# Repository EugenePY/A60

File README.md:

# Forest 65 PCB

Hi, Andrew nice work!

Since you are using the web based eda tool, I generaly do not have any problems 
with them. It's very simple and having great integration with the pcb/eletronic 
component firms, but I suggest you still need to learn KiCAD, 

There are few benifit about kicad. 

1. it's open sourced.
2. it has a great supported by the eda/keyboard community.

Most of open sourced EE project are using kicad as their tools, and some of 
professional still prefer it to some commercial EDAs like EAGLE, Altium. 

there are many learning resource for kicad, one of most popular one is the 
[Ai03's Keyboard Guide](https://wiki.ai03.com/books/pcb-design/page/pcb-guide-part-1---preparations)

You may follow it to know how to use kicad. Kicad also has a lot of open sourced footprint libarary.

1. [Ai03's Mx Switch Footprint](https://github.com/ai03-2725/MX_Alps_Hybrid.git)
2. [Acherion Project Gondolindrim](https://github.com/AcheronProject)

# For current PCB files

I  add datasheet about ATMEGA32U4-AU, you can check your pins, reading the 
datasheet maybe very overwhelming in the first place, but I still recommanded 
to go through it. It's very benifitcial for you in the long run since you want 
to get into eletronic desin/EE. And other datasheet follows the similar priciple.

# TODOs

1. Please rewire your pcb in kicad.

# PCB comments

I think your pcb works, but there are few things need to be improved.
    
### The wire should not be too close to the pcb edge if the space allowed. 

    If the wire are too close to the edge it may break easily, but it just a 
    minor things to notice, generaly it does not affect overall functionality.

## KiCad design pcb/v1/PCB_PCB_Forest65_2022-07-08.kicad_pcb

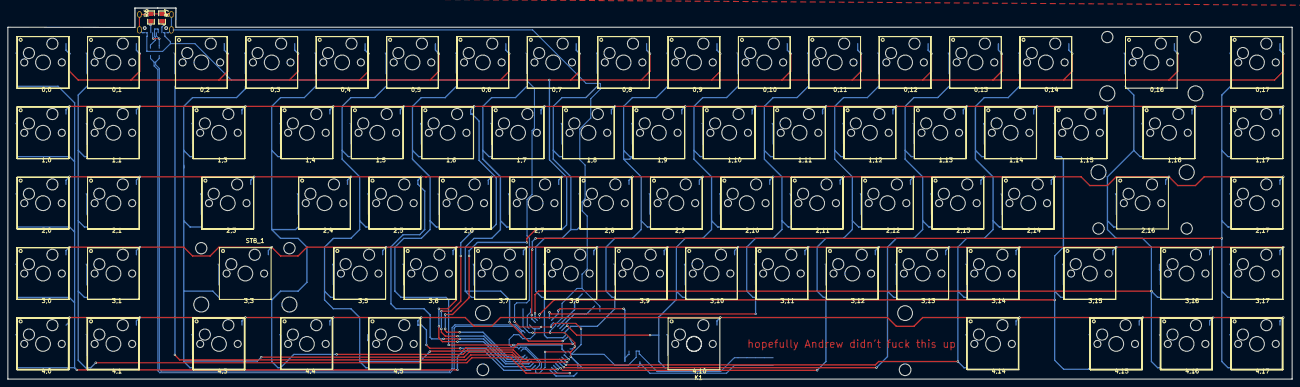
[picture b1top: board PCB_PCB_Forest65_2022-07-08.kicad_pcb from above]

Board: 2 copper layers, 347.6 x 100.4 mm, 174 parts (0 on the bottom side), 112 nets.

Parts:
0,0, 0,1, 0,2, 0,3, 0,4, 0,5, 0,6, 0,7, 0,8, 0,9, 0,10, 0,11, 0,12, 0,13, 0,14, 0,16, 0,17, 1,0, 1,1, 1,3, 1,4, 1,5, 1,6, 1,7, 1,8, 1,9, 1,10, 1,11, 1,12, 1,13, 1,14, 1,15, 1,16, 1,17, 2,0, 2,1, 2,3, 2,4, 2,5, 2,6, 2,7, 2,8, 2,9, 2,10, 2,11, 2,12, 2,13, 2,14, 2,16, 2,17, 3,0, 3,1, 3,3, 3,5, 3,6, 3,7, 3,8, 3,9, 3,10, 3,11, 3,12, 3,13, 3,14, 3,15, 3,16, 3,17, 4,0, 4,1, 4,3, 4,4, 4,5, 4,10, 4,14, 4,15, 4,16, 4,17: 凯华热插拔; 凯华热插拨
C1, C2: 22pF; C0805
C3: 1uF; C0805
C4, C5, C6, C7: 100nF; C0805
C8: 470nF; C0805
D1, D2, D3, D4, D5, D6, D7, D8, D9, D10, D11, D12, D13, D14, D15, D16, D17, D18, D19, D20, D21, D22, D23, D24, D25, D26, D27, D28, D29, D30, D31, D32, D33, D34, D35, D36, D37, D38, D39, D40, D41, D42, D43, D44, D45, D46, D47, D48, D49, D50, D51, D52, D53, D54, D55, D56, D57, D58, D59, D60, D61, D62, D63, D64, D65, D66, D67, D68, D69, D70, D74, D75, D76, D77, D81, D82: 1N4148W; SOD-123_L2.8-W1.8-LS3.7-RD
K1: PCB卫星轴7U; CHERRY_MX_7U
KEY1: Switch3x4x2; SW-SMD_L4.0-W2.9-LS5.0
R1, R2: 10K; R0805
R3, R4: 22; R0805
R6, R7: 5.1K; R0805
STB_1, STB_2, STB_3: Cherry MX 2u Stabilizer; MX1A STABILIZER 2U
U1: ATMEGA32U4-AU; QFP-44_L10.0-W10.0-P0.80-LS13.2-BL
USBC1: TYPE-C-31-M-12; USB-C_SMD-TYPE-C-31-M-12
X1: 16mhz; OSC-SMD_2P-L5.0-W3.2

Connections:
0,0_K2: 0,0.K2, D1.2
0,2_K2: 0,2.K2, D3.2
0,5_K2: 0,5.K2, D6.2
0,7_K2: 0,7.K2, D8.2
0,9_K2: 0,9.K2, D10.2
0,11_K2: 0,11.K2, D12.2
0,12_K2: 0,12.K2, D13.2
0,14_K2: 0,14.K2, D15.2
0,17_K2: 0,17.K2, D17.2
1,1_K2: 1,1.K2, D33.2
1,4_K2: 1,4.K2, D31.2
1,5_K2: 1,5.K2, D27.2
1,7_K2: 1,7.K2, D29.2
1,9_K2: 1,9.K2, D19.2
1,11_K2: 1,11.K2, D21.2
1,14_K2: 1,14.K2, D25.2
1,16_K2: 1,16.K2, D23.2
2,0_K2: 2,0.K2, D35.2
2,6_K2: 2,6.K2, D41.2
2,8_K2: 2,8.K2, D39.2
2,10_K2: 2,10.K2, D49.2
2,12_K2: 2,12.K2, D47.2
2,13_K2: 2,13.K2, D43.2
2,17_K2: 2,17.K2, D51.2
3,1_K2: 3,1.K2, D65.2
3,5_K2: 3,5.K2, D63.2
3,6_K2: 3,6.K2, D59.2
3,8_K2: 3,8.K2, D61.2
3,10_K2: 3,10.K2, D52.2
3,12_K2: 3,12.K2, D54.2
3,15_K2: 3,15.K2, D57.2
3,16_K2: 3,16.K2, D56.2
4,0_K2: 4,0.K2, D67.2
4,3_K2: 4,3.K2, D69.2
4,14_K2: 4,14.K2, D75.2
4,17_K2: 4,17.K2, D82.2
COL0: D1.1, D34.1, D35.1, D66.1, D67.1, U1.36
COL1: D2.1, D33.1, D36.1, D65.1, D68.1, U1.32
COL2: D3.1, U1.31
COL3: D4.1, D32.1, D37.1, D64.1, D69.1, U1.27
COL4: D5.1, D31.1, D38.1, D70.1, U1.26
COL5: D6.1, D27.1, D42.1, D63.1, D74.1, U1.22
COL6: D7.1, D28.1, D41.1, D59.1, U1.25
COL7: D8.1, D29.1, D40.1, D60.1, U1.21
COL8: D9.1, D30.1, D39.1, D61.1, U1.20
COL9: D10.1, D19.1, D50.1, D62.1, U1.19
COL10: D11.1, D20.1, D49.1, D52.1, D81.1, U1.18
COL11: D12.1, D21.1, D48.1, D53.1, U1.12
COL12: D13.1, D22.1, D47.1, D54.1, U1.30
COL13: D14.1, D26.1, D43.1, D55.1, U1.29
COL14: D15.1, D25.1, D44.1, D58.1, D75.1, U1.28
COL15: D24.1, D57.1, D76.1, U1.11
COL16: D16.1, D23.1, D46.1, D56.1, D77.1, U1.10
COL17: D17.1, D18.1, D45.1, D51.1, D82.1, U1.9
D2_2: 0,1.K2, D2.2
D4_2: 0,3.K2, D4.2
D5_2: 0,4.K2, D5.2
D7_2: 0,6.K2, D7.2
D9_2: 0,8.K2, D9.2
D11_2: 0,10.K2, D11.2
D14_2: 0,13.K2, D14.2
D16_2: 0,16.K2, D16.2
D18_2: 1,17.K2, D18.2
D20_2: 1,10.K2, D20.2
D22_2: 1,12.K2, D22.2
D24_2: 1,15.K2, D24.2
D26_2: 1,13.K2, D26.2
D28_2: 1,6.K2, D28.2
D30_2: 1,8.K2, D30.2
D32_2: 1,3.K2, D32.2
D34_2: 1,0.K2, D34.2
D36_2: 2,1.K2, D36.2
D37_2: 2,3.K2, D37.2
D38_2: 2,4.K2, D38.2
D40_2: 2,7.K2, D40.2
D42_2: 2,5.K2, D42.2
D44_2: 2,14.K2, D44.2
D45_2: 3,17.K2, D45.2
D46_2: 2,16.K2, D46.2
D48_2: 2,11.K2, D48.2
D50_2: 2,9.K2, D50.2
D53_2: 3,11.K2, D53.2
D55_2: 3,13.K2, D55.2
D58_2: 3,14.K2, D58.2
D60_2: 3,7.K2, D60.2
D62_2: 3,9.K2, D62.2
D64_2: 3,3.K2, D64.2
D66_2: 3,0.K2, D66.2
D68_2: 4,1.K2, D68.2
D70_2: 4,4.K2, D70.2
D74_2: 4,5.K2, D74.2
D76_2: 4,15.K2, D76.2
D77_2: 4,16.K2, D77.2
D81_2: 4,10.K2, D81.2
D+: R4.1, U1.4
D-: R3.2, U1.3
GND: C1.1, C2.1, C3.1, C4.1, C5.1, C6.1, C7.1, C8.2, KEY1.2, R2.2, R6.2, R7.1, U1.5, U1.15, U1.23, U1.35, U1.43, USBC1.0, USBC1.A1, USBC1.A12, USBC1.B1, USBC1.B12
RESET: KEY1.1, R1.2, U1.13
ROW0: 0,0.K1, 0,1.K1, 0,2.K1, 0,3.K1, 0,4.K1, 0,5.K1, 0,6.K1, 0,7.K1, 0,8.K1, 0,9.K1, 0,10.K1, 0,11.K1, 0,12.K1, 0,13.K1, 0,14.K1, 0,16.K1, 0,17.K1, U1.41
ROW1: 1,0.K1, 1,1.K1, 1,3.K1, 1,4.K1, 1,5.K1, 1,6.K1, 1,7.K1, 1,8.K1, 1,9.K1, 1,10.K1, 1,11.K1, 1,12.K1, 1,13.K1, 1,14.K1, 1,15.K1, 1,16.K1, 1,17.K1, U1.40
ROW2: 2,0.K1, 2,1.K1, 2,3.K1, 2,4.K1, 2,5.K1, 2,6.K1, 2,7.K1, 2,8.K1, 2,9.K1, 2,10.K1, 2,11.K1, 2,12.K1, 2,13.K1, 2,14.K1, 2,16.K1, 2,17.K1, U1.39
ROW3: 3,0.K1, 3,1.K1, 3,3.K1, 3,5.K1, 3,6.K1, 3,7.K1, 3,8.K1, 3,9.K1, 3,10.K1, 3,11.K1, 3,12.K1, 3,13.K1, 3,14.K1, 3,15.K1, 3,16.K1, 3,17.K1, U1.38
ROW4: 4,0.K1, 4,1.K1, 4,3.K1, 4,4.K1, 4,5.K1, 4,10.K1, 4,14.K1, 4,15.K1, 4,16.K1, 4,17.K1, U1.37
U1_6: C3.2, U1.6
U1_16: C1.2, U1.16, X1.1
U1_17: C2.2, U1.17, X1.2
U1_33: R2.1, U1.33
USBC1_A5: R6.1, USBC1.A5
USBC1_B5: R7.2, USBC1.B5
USBC1_B6: R3.1, USBC1.A6, USBC1.B6
USBC1_B7: R4.2, USBC1.A7, USBC1.B7
VCC: C4.2, C5.2, C6.2, C7.2, C8.1, R1.1, U1.2, U1.7, U1.14, U1.24, U1.34, U1.44, USBC1.A4, USBC1.A9, USBC1.B4, USBC1.B9

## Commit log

2022-07-05 fix typo
2022-07-05 the pcb files
    Thanks a lot man!
    我用的軟體是立創eda因爲他們從畫圖到生產一套系統在中國很方便
    just incase if it might not work
    我有轉一個kicad的版本但是原理圖沒辦法一起轉所以我把它導出成一個pdf了
    also 我後來研究了一下最後使用的是GitHub desktop 還蠻簡單易懂的
    gn!
2022-07-06 Add docs/ rewrite README.md
2022-07-06 rewrite README.md
2022-07-07 Firmware files
2022-07-07 pcb route fix
2022-07-07 firmware mod starts
2022-07-07 Firmware is now compilable
    roughly modded the Sunsetter firmware
2022-07-23 playing around with firmware
2022-07-23 mod info.json
2022-07-23 Via enable
2022-07-24 lower case
2022-07-24 fixing the naming
2022-07-24 file name lowercase
2022-07-24 more lower case fix
2022-07-24 lowercase for firmware
2022-08-30 add STEP files
2022-08-30 renders
2022-09-11 add firmware and via file
2022-11-18 update pcb files
2022-11-20 added photo
2023-04-21 update vendor id
    0x1127
2023-08-10 Update VIA definition to V3
2023-08-10 revert VIA version back to V2
